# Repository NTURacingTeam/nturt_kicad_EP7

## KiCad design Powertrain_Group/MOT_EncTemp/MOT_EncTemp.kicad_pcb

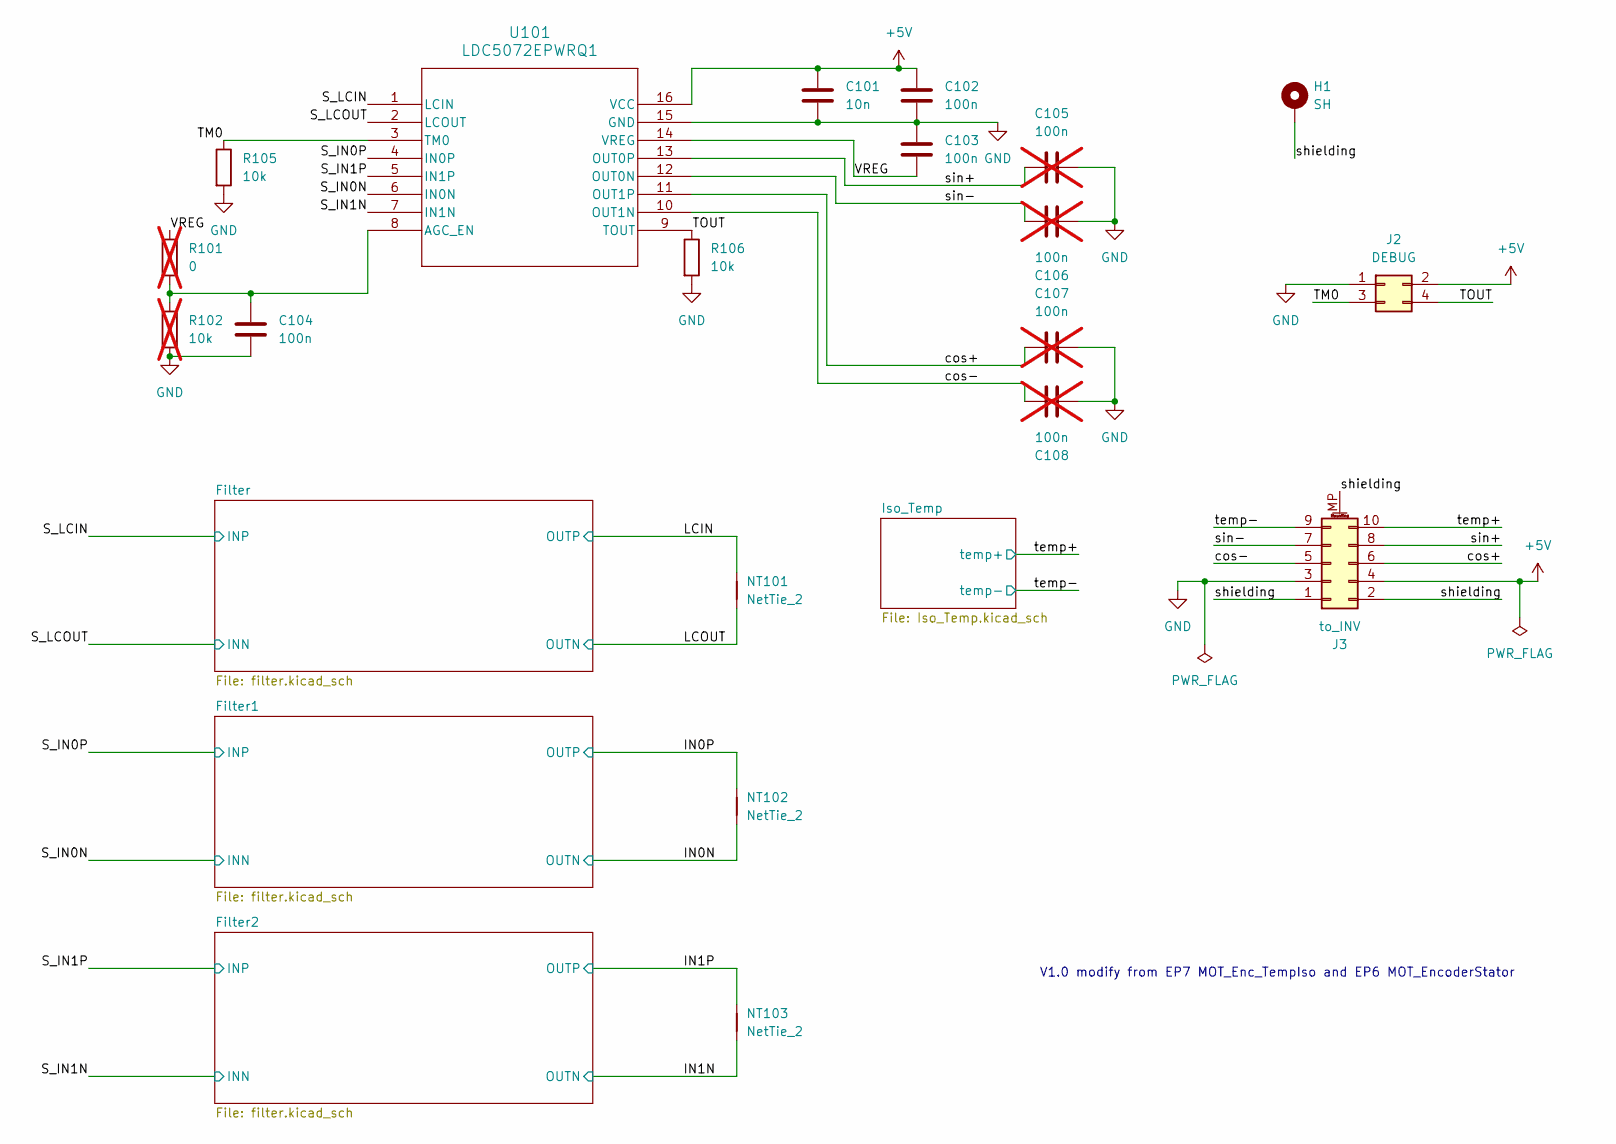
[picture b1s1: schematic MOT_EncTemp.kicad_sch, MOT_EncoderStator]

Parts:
C101: 10n; C_0402_1005Metric
C102, C103: 100n; C_0402_1005Metric
C104: 100n; C_0603_1608Metric
C105, C106, C107, C108: 100n; C_0402_1005Metric; not fitted
H1: SH; MountingHole_3.2mm_M3_Pad_Via
J2: DEBUG; PinHeader_2x02_P2.00mm_Vertical_SMD
J3: to_INV; CONN_2202010000-SD_10P_MOL
NT101, NT102, NT103: NetTie_2; NetTie-2_SMD_Pad0.5mm
R101: 0; R_0603_1608Metric; not fitted
R102: 10k; R_0603_1608Metric; not fitted
R105, R106: 10k; R_0402_1005Metric
U101: LDC5072EPWRQ1; TSSOP-16_4.4x5mm_P0.65mm

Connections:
+5V: C101.1, C102.1, J2.2, J3.4, U101.16 (VCC); also elsewhere on the board
/IN0N: NT102.1; also elsewhere on the board
/IN0P: NT102.2; also elsewhere on the board
/IN1N: NT103.1; also elsewhere on the board
/IN1P: NT103.2; also elsewhere on the board
/LCIN: NT101.2; also elsewhere on the board
/LCOUT: NT101.1; also elsewhere on the board
/S_IN0N: U101.6 (IN0N); also elsewhere on the board
/S_IN0P: U101.4 (IN0P); also elsewhere on the board
/S_IN1N: U101.7 (IN1N); also elsewhere on the board
/S_IN1P: U101.5 (IN1P); also elsewhere on the board
/S_LCIN: U101.1 (LCIN); also elsewhere on the board
/S_LCOUT: U101.2 (LCOUT); also elsewhere on the board
/TM0: J2.3, R105.1, U101.3 (TM0)
/TOUT: J2.4, R106.1, U101.9 (TOUT)
/VREG: C103.2, R101.1, U101.14 (VREG)
/cos+: C107.1, J3.6, U101.11 (OUT1P)
/cos-: C108.2, J3.5, U101.10 (OUT1N)
/shielding: H1.1, J3.1, J3.2, J3.MP (MountPin)
/sin+: C105.1, J3.8, U101.13 (OUT0P)
/sin-: C106.2, J3.7, U101.12 (OUT0N)
/temp+: J3.10; also elsewhere on the board
/temp-: J3.9; also elsewhere on the board
GND: C101.2, C102.2, C103.1, C104.2, C105.2, C106.1, C107.2, C108.1, J2.1, J3.3, R102.2, R105.2, R106.2, U101.15 (GND); also elsewhere on the board
unnamed: C104.1, R101.2, R102.1, U101.8 (AGC_EN)

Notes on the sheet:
V1.0 modify from EP7 MOT_Enc_TempIso and EP6 MOT_EncoderStator

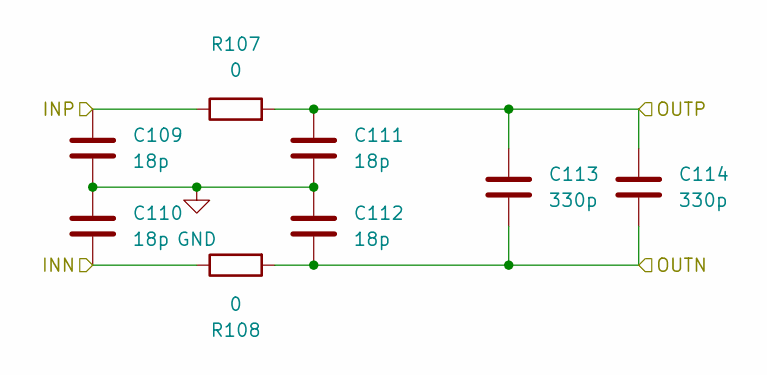
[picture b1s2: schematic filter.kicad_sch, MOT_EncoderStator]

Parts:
C109, C110, C111, C112: 18p; C_0402_1005Metric
C113, C114: 330p; C_0402_1005Metric
R107, R108: 0; R_0402_1005Metric

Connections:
/LCIN: C111.1, C113.1, C114.1, R107.2; also elsewhere on the board
/LCOUT: C112.2, C113.2, C114.2, R108.2; also elsewhere on the board
/S_LCIN: C109.1, R107.1; also elsewhere on the board
/S_LCOUT: C110.2, R108.1; also elsewhere on the board
GND: C109.2, C110.1, C111.2, C112.1; also elsewhere on the board

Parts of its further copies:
C115, C116, C117, C118, C121, C122, C123, C124: 18p; C_0402_1005Metric
C119, C120, C125, C126: 330p; C_0402_1005Metric
R109, R110, R111, R112: 0; R_0402_1005Metric

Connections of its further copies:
/IN0N: C118.2, C119.2, C120.2, R110.2; also elsewhere on the board
/IN0P: C117.1, C119.1, C120.1, R109.2; also elsewhere on the board
/IN1N: C124.2, C125.2, C126.2, R112.2; also elsewhere on the board
/IN1P: C123.1, C125.1, C126.1, R111.2; also elsewhere on the board
/S_IN0N: C116.2, R110.1; also elsewhere on the board
/S_IN0P: C115.1, R109.1; also elsewhere on the board
/S_IN1N: C122.2, R112.1; also elsewhere on the board
/S_IN1P: C121.1, R111.1; also elsewhere on the board
GND: C115.2, C116.1, C117.2, C118.1, C121.2, C122.1, C123.2, C124.1; also elsewhere on the board

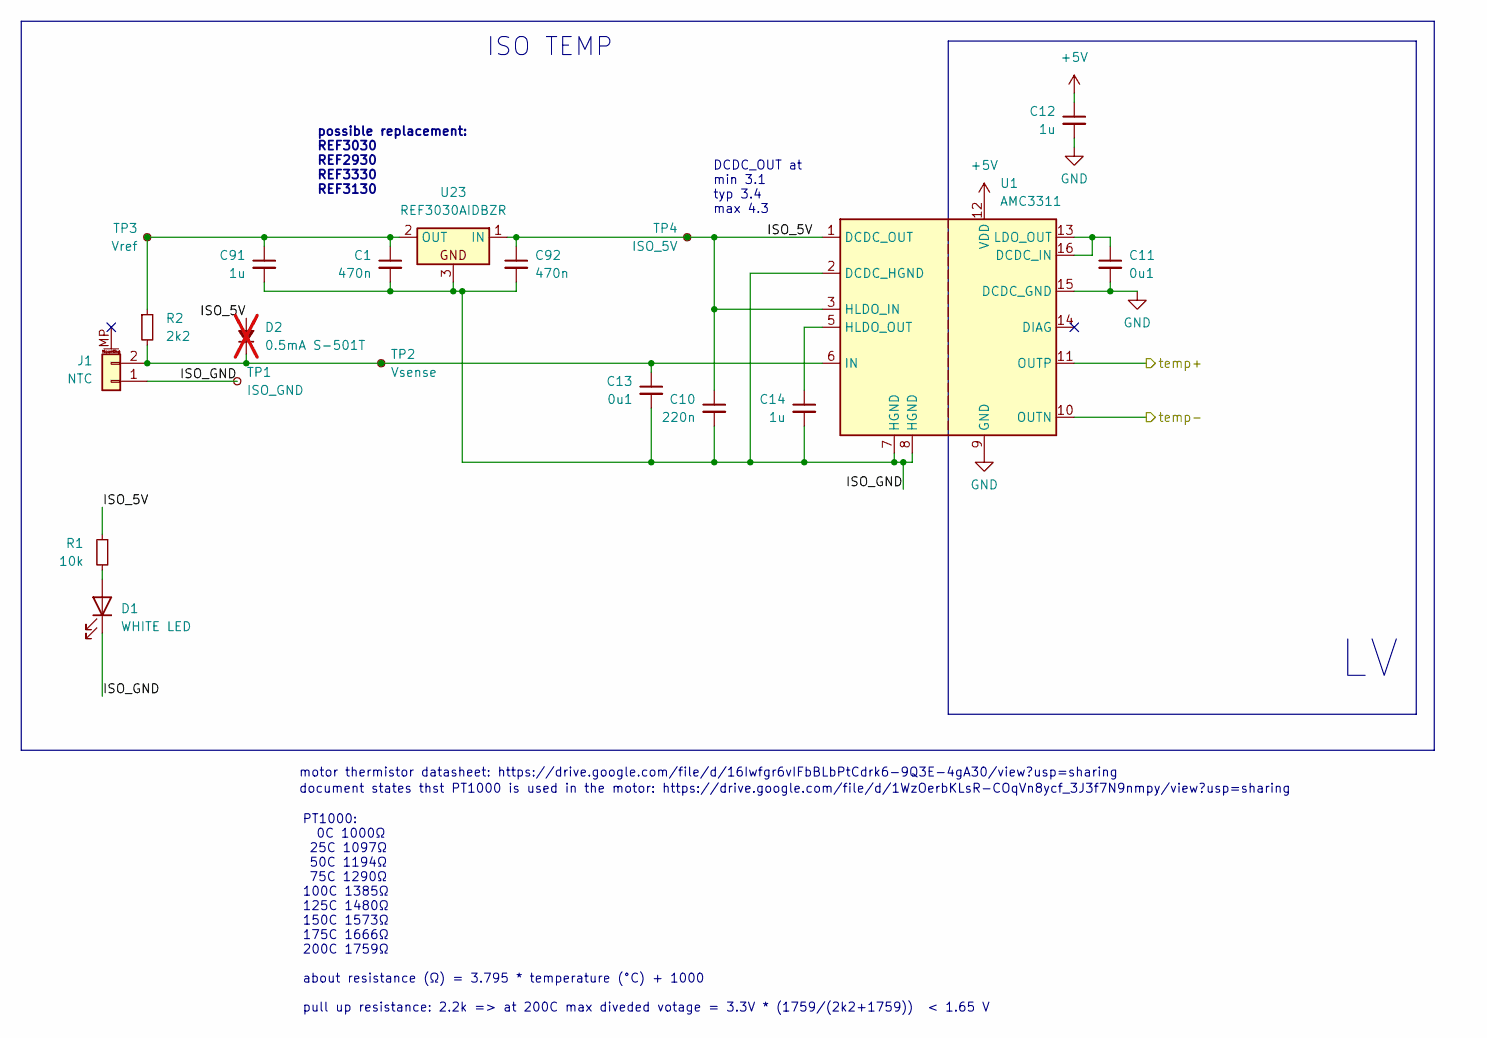
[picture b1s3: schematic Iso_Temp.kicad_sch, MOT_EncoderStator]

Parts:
C1, C92: 470n; C_0603_1608Metric_Pad1.08x0.95mm_HandSolder
C10: 220n; C_0603_1608Metric_Pad1.08x0.95mm_HandSolder
C11, C13: 0u1; C_0603_1608Metric_Pad1.08x0.95mm_HandSolder
C12, C14, C91: 1u; C_0603_1608Metric_Pad1.08x0.95mm_HandSolder
D1: WHITE LED; LED_0603_1608Metric_Pad1.05x0.95mm_HandSolder
D2: 0.5mA S-501T; D_1206_3216Metric_Pad1.42x1.75mm_HandSolder; not fitted
J1: NTC; JST_PH_S2B-PH-SM4-TB_1x02-1MP_P2.00mm_Horizontal
R1: 10k; R_0603_1608Metric_Pad0.98x0.95mm_HandSolder
R2: 2k2; R_0603_1608Metric_Pad0.98x0.95mm_HandSolder
TP1: ISO_GND; TestPoint_Pad_D1.0mm
TP2: Vsense; TestPoint_Pad_D1.0mm
TP3: Vref; TestPoint_Pad_D1.0mm
TP4: ISO_5V; TestPoint_Pad_D1.0mm
U1: AMC3311; SOIC-16W_7.5x10.3mm_P1.27mm
U23: REF3030AIDBZR; SOT-23

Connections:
+5V: C12.1, U1.12 (VDD); also elsewhere on the board
/Iso_Temp/ISO_5V: C10.1, C92.1, D2.2 (A), R1.1, TP4.1, U1.1 (DCDC_OUT), U1.3 (HLDO_IN), U23.1 (IN)
/Iso_Temp/ISO_GND: C1.2, C10.2, C13.2, C14.2, C91.2, C92.2, D1.1 (K), J1.1, TP1.1, U1.2 (DCDC_HGND), U1.7 (HGND), U1.8 (HGND), U23.3
/temp+: U1.11 (OUTP); also elsewhere on the board
/temp-: U1.10 (OUTN); also elsewhere on the board
GND: C11.2, C12.2, U1.9 (GND), U1.15 (DCDC_GND); also elsewhere on the board
unnamed: D1.2 (A), R1.2
unnamed: C13.1, D2.1 (K), J1.2, R2.2, TP2.1, U1.6 (IN)
unnamed: C11.1, U1.13 (LDO_OUT), U1.16 (DCDC_IN)
unnamed: C14.1, U1.5 (HLDO_OUT)
unnamed: C1.1, C91.1, R2.1, TP3.1, U23.2 (OUT)

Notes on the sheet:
possible replacement: REF3030 REF2930 REF3330 REF3130
motor thermistor datasheet: https://drive.google.com/file/d/16Iwfgr6vIFbBLbPtCdrk6-9Q3E-4gA30/view?usp=sharing
PT1000: 0C 1000Ω 25C 1097Ω 50C 1194Ω 75C 1290Ω 100C 1385Ω 125C 1480Ω 150C 1573Ω 175C 1666Ω 200C 1759Ω about resistance (Ω) = 3.795 * temperature (°C) + 1000 pull up resistance: 2.2k => at 200C max diveded votage = 3.3V * (1759/(2k2+1759)) < 1.65 V
ISO TEMP
DCDC_OUT at min 3.1 typ 3.4 max 4.3
document states thst PT1000 is used in the motor: https://drive.google.com/file/d/1WzOerbKLsR-COqVn8ycf_3J3f7N9nmpy/view?usp=sharing

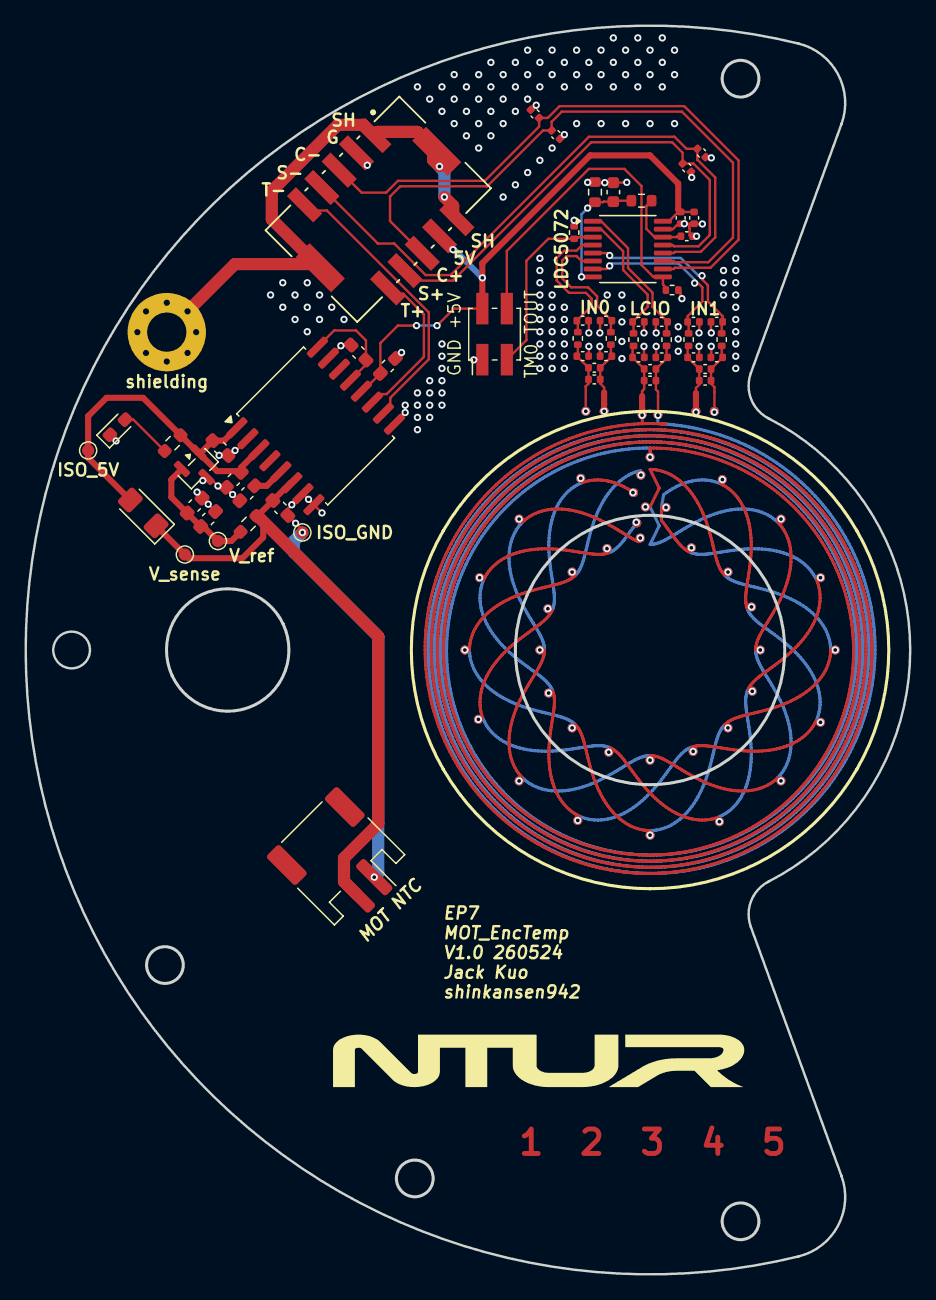
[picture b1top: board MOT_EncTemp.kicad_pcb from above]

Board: 4 copper layers, 72.2 x 102.0 mm, 62 parts (0 on the bottom side), 32 nets.

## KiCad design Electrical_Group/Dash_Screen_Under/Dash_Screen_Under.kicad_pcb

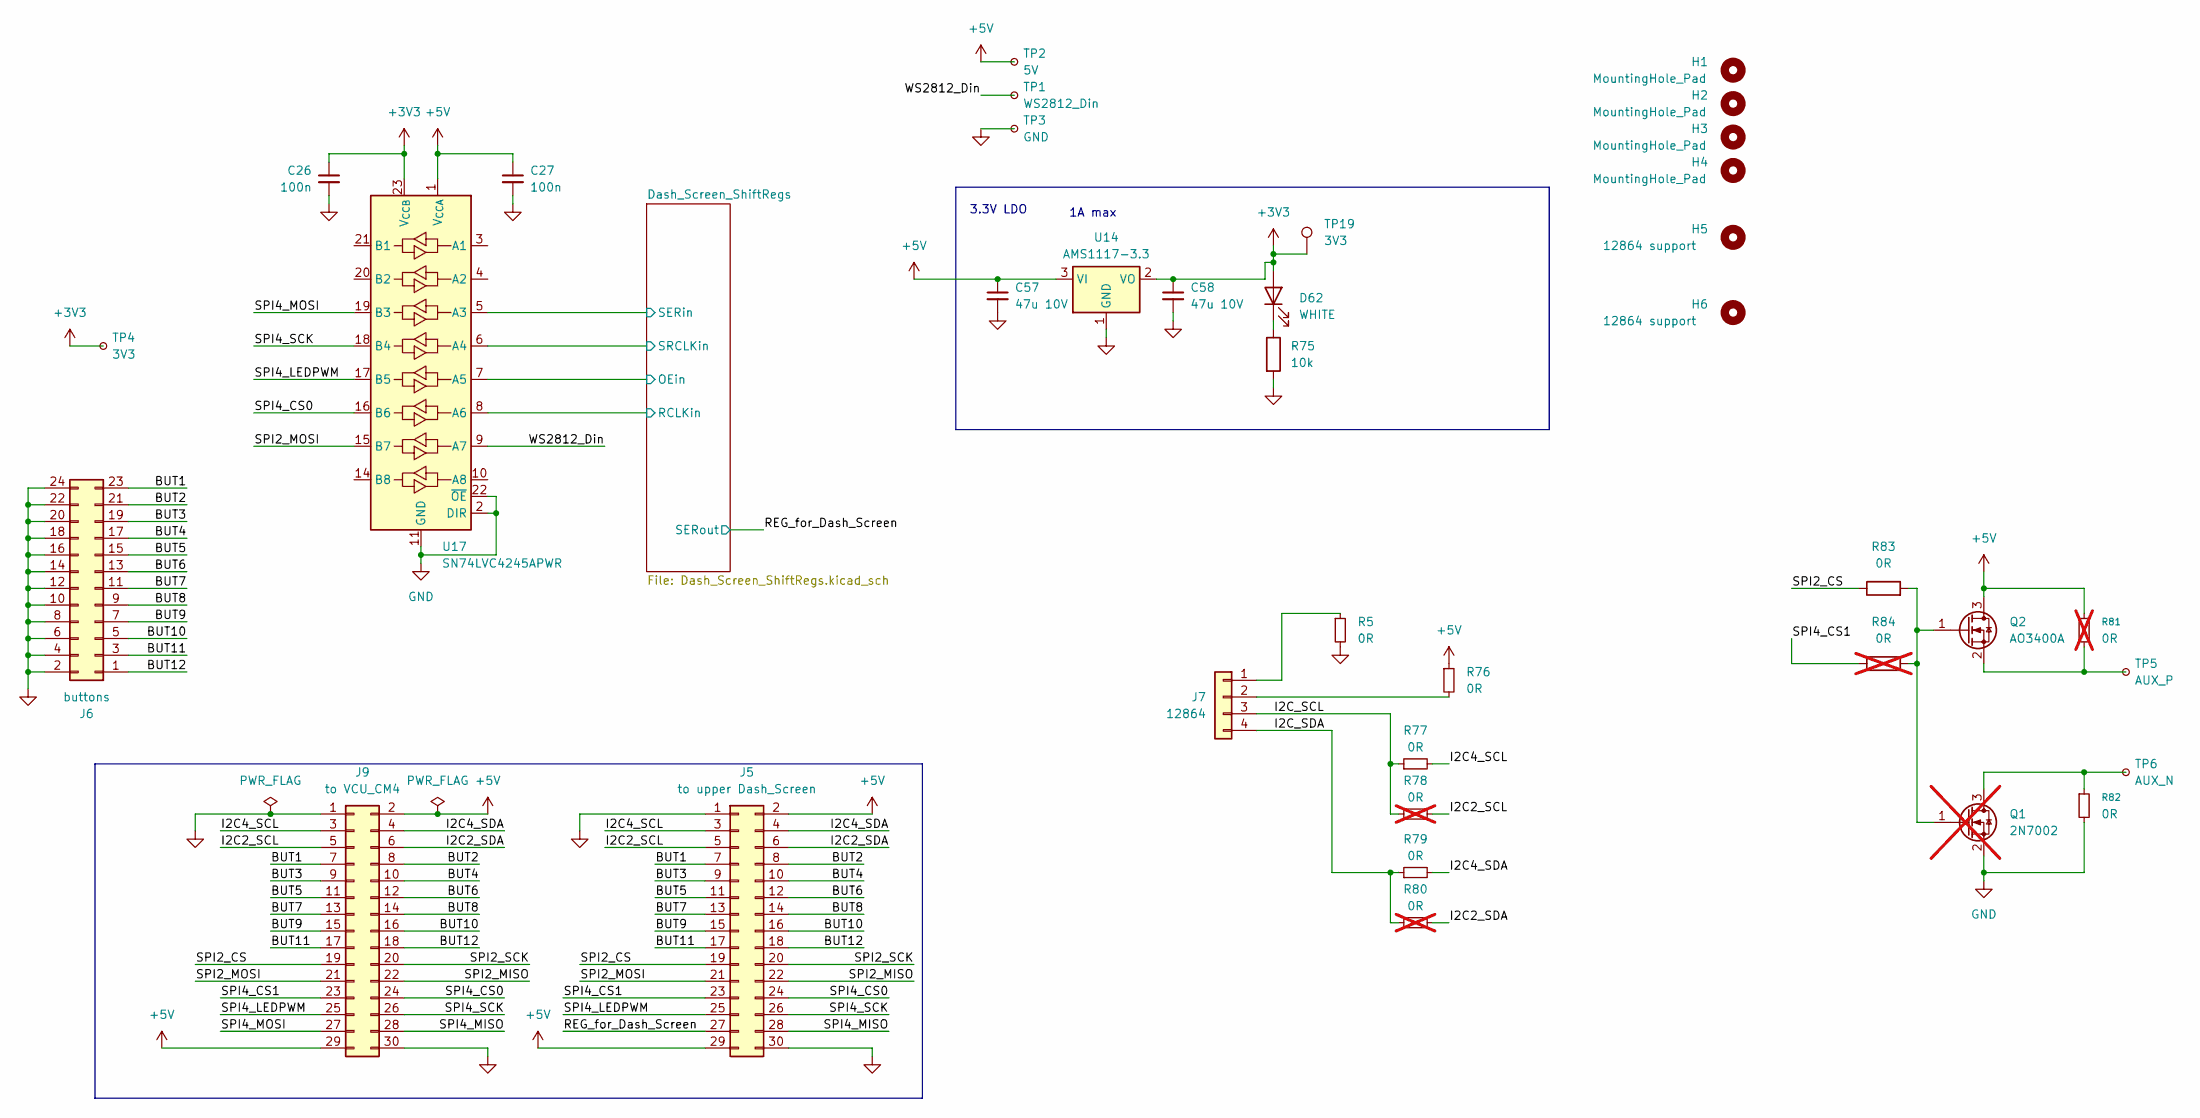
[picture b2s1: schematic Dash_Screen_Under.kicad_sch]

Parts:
C26, C27: 100n; C_0603_1608Metric
C57, C58: 47u 10V; C_1206_3216Metric
D62: WHITE; LED_0603_1608Metric
H1, H2, H3, H4: MountingHole_Pad; MountingHole_3.2mm_M3
H5, H6: 12864 support; MountingHole_3.2mm_M3
J5: to upper Dash_Screen; PinHeader_2x15_P2.00mm_Vertical_SMD
J6: buttons; PinHeader_2x12_P2.00mm_Horizontal
J7: 12864; 12864_1.3_I2C
J9: to VCU_CM4; PinSocket_2x15_P2.00mm_Vertical_SMD
Q1: 2N7002; SOT-23; not fitted
Q2: AO3400A; SOT-23
R5, R76, R77, R79, R82: 0R; R_0805_2012Metric_Pad1.20x1.40mm_HandSolder
R75: 10k; R_0603_1608Metric
R78, R80, R81: 0R; R_0805_2012Metric_Pad1.20x1.40mm_HandSolder; not fitted
R83: 0R; R_0603_1608Metric
R84: 0R; R_0603_1608Metric; not fitted
TP1: WS2812_Din; edge_pad_1.4mm_0.7mm
TP2: 5V; edge_pad_1.4mm_0.7mm
TP3: GND; edge_pad_1.4mm_0.7mm
TP4: 3V3; edge_pad_1.4mm_0.7mm
TP5: AUX_P; edge_pad_1.4mm_0.7mm
TP6: AUX_N; edge_pad_1.4mm_0.7mm
TP19: 3V3; TestPoint_Pad_D1.0mm
U14: AMS1117-3.3; SOT-223-3_TabPin2
U17: SN74LVC4245APWR; TSSOP-24_4.4x7.8mm_P0.65mm

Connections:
+3V3: C26.1, C58.1, D62.2 (A), TP4.1, TP19.1, U14.2 (VO), U17.23 (V_{CCB}), U17.24 (V_{CCB})
+5V: C27.1, C57.1, J5.2, J5.29, J9.2, J9.29, Q2.3 (D), R76.1, R81.1, TP2.1, U14.3 (VI), U17.1 (V_{CCA}); also elsewhere on the board
/BUT1: J5.7, J6.23, J9.7
/BUT2: J5.8, J6.21, J9.8
/BUT3: J5.9, J6.19, J9.9
/BUT4: J5.10, J6.17, J9.10
/BUT5: J5.11, J6.15, J9.11
/BUT6: J5.12, J6.13, J9.12
/BUT7: J5.13, J6.11, J9.13
/BUT8: J5.14, J6.9, J9.14
/BUT9: J5.15, J6.7, J9.15
/BUT10: J5.16, J6.5, J9.16
/BUT11: J5.17, J6.3, J9.17
/BUT12: J5.18, J6.1, J9.18
/Dash_Screen_ShiftRegs/OE: U17.7 (A5); also elsewhere on the board
/Dash_Screen_ShiftRegs/RCLK: U17.8 (A6); also elsewhere on the board
/Dash_Screen_ShiftRegs/SER: U17.5 (A3); also elsewhere on the board
/Dash_Screen_ShiftRegs/SRCLK: U17.6 (A4); also elsewhere on the board
/I2C2_SCL: J5.5, J9.5, R78.2
/I2C2_SDA: J5.6, J9.6, R80.2
/I2C4_SCL: J5.3, J9.3, R77.2
/I2C4_SDA: J5.4, J9.4, R79.2
/I2C_SCL: J7.3, R77.1, R78.1
/I2C_SDA: J7.4, R79.1, R80.1
/REG_for_Dash_Screen: J5.27; also elsewhere on the board
/SPI2_CS: J5.19, J9.19, R83.1
/SPI2_MISO: J5.22, J9.22
/SPI2_MOSI: J5.21, J9.21, U17.15 (B7)
/SPI2_SCK: J5.20, J9.20
/SPI4_CS0: J5.24, J9.24, U17.16 (B6)
/SPI4_CS1: J5.23, J9.23, R84.1
/SPI4_LEDPWM: J5.25, J9.25, U17.17 (B5)
/SPI4_MISO: J5.28, J9.28
/SPI4_MOSI: J9.27, U17.19 (B3)
/SPI4_SCK: J5.26, J9.26, U17.18 (B4)
/WS2812_Din: TP1.1, U17.9 (A7)
GND: C26.2, C27.2, C57.2, C58.2, J5.1, J5.30, J6.2, J6.4, J6.6, J6.8, J6.10, J6.12, J6.14, J6.16, J6.18, J6.20, J6.22, J6.24, J9.1, J9.30, Q1.2 (S), R5.2, R75.2, R82.2, TP3.1, U14.1 (GND), U17.2 (DIR), U17.11 (GND), U17.12 (GND), U17.13 (GND), U17.22 (~OE); also elsewhere on the board
unnamed: D62.1 (K), R75.1
unnamed: J7.1, R5.1
unnamed: J7.2, R76.2
unnamed: Q1.3 (D), R82.1, TP6.1
unnamed: Q1.1 (G), Q2.1 (G), R83.2, R84.2
unnamed: Q2.2 (S), R81.2, TP5.1

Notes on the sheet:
3.3V LDO
1A max

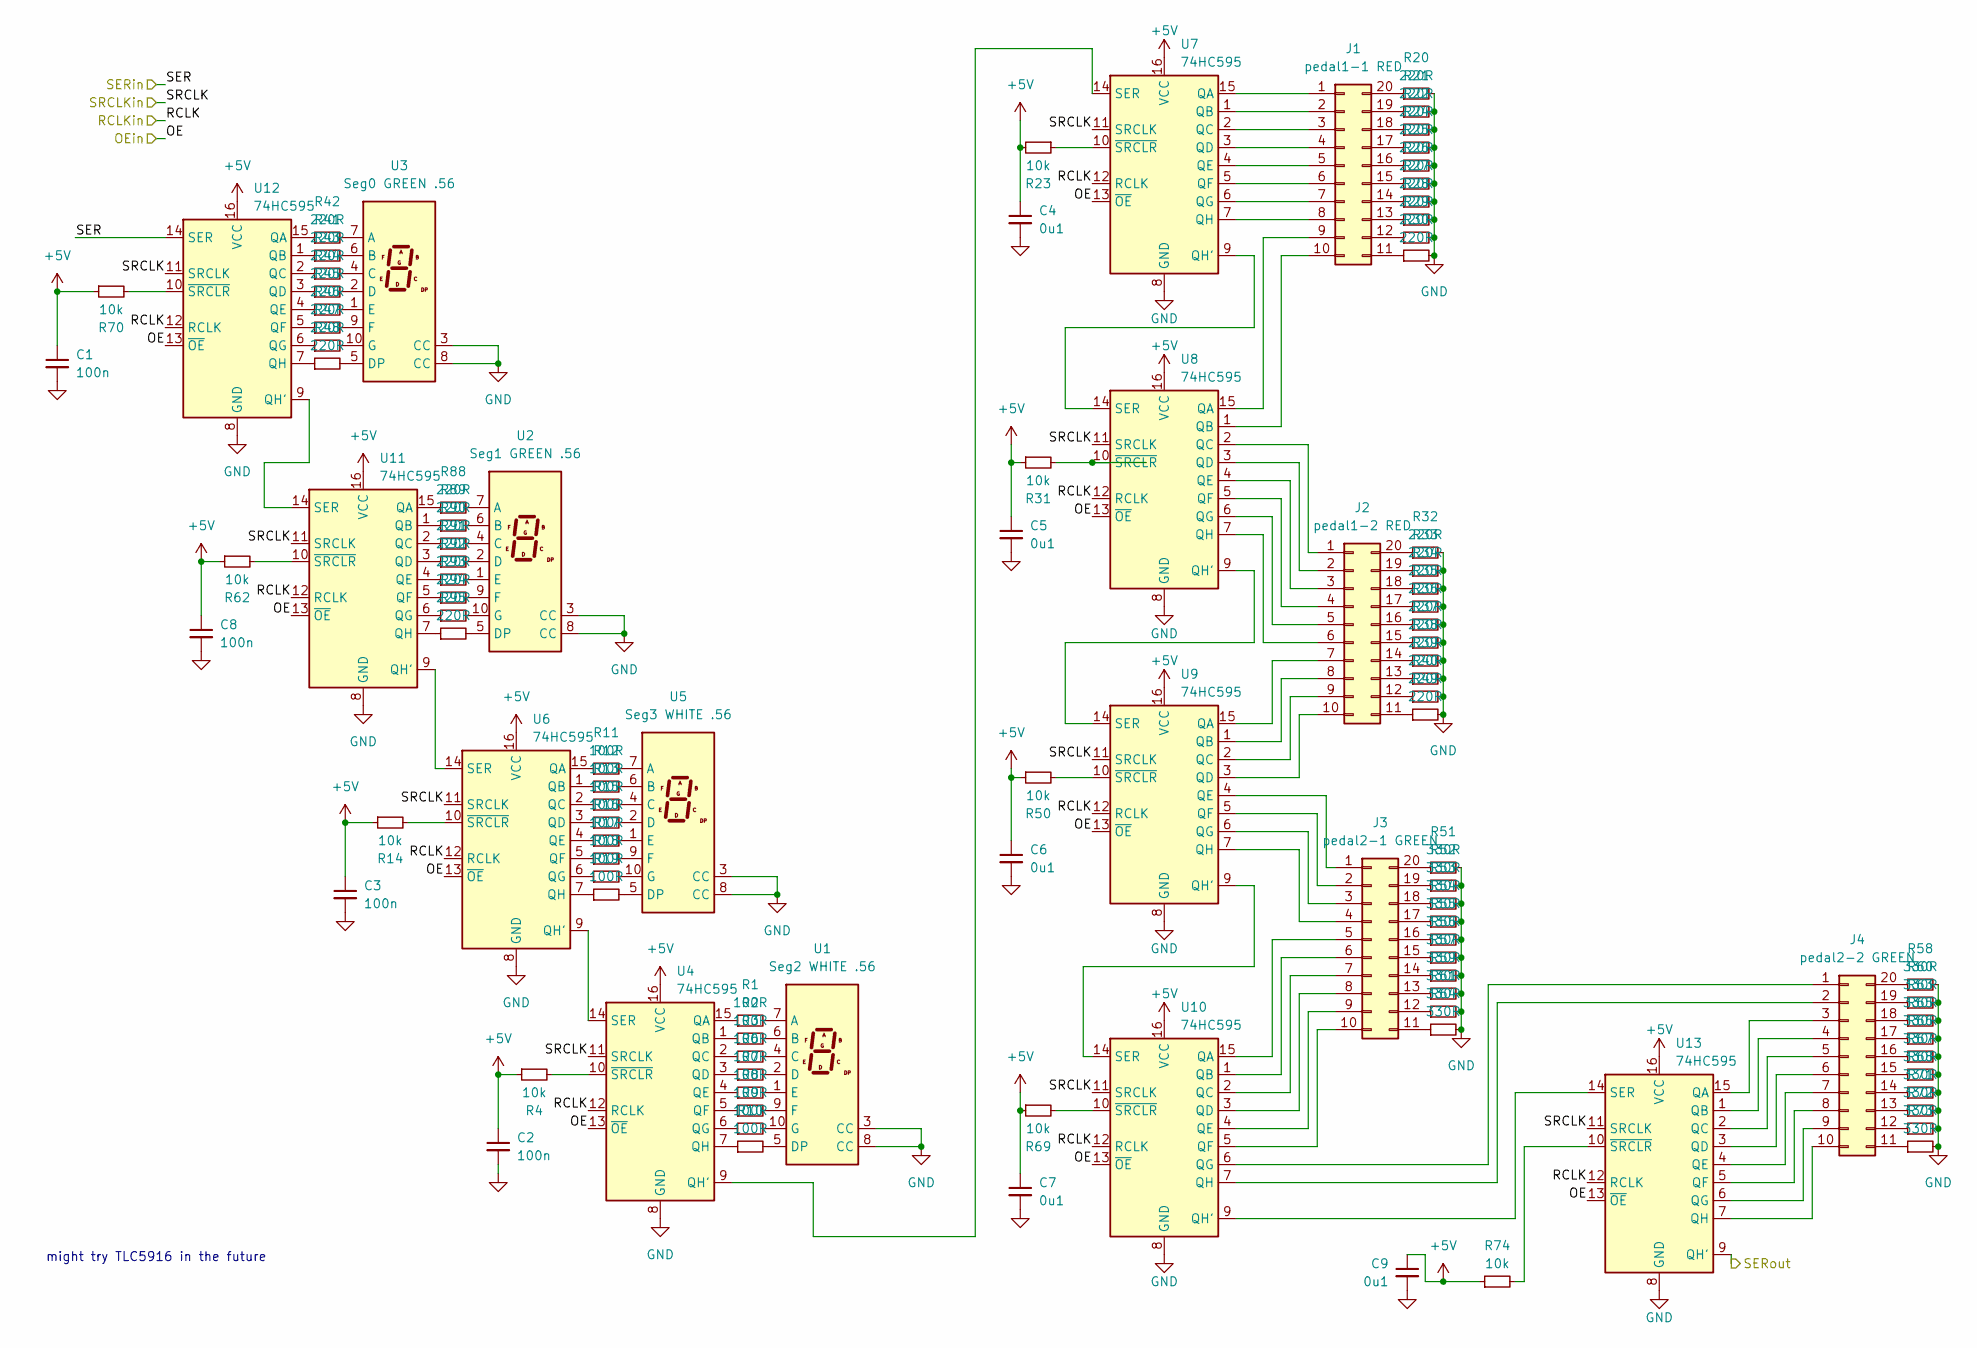
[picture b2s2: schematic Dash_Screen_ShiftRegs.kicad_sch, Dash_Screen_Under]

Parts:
C1, C2, C3, C8: 100n; C_0603_1608Metric
C4, C5, C6, C7, C9: 0u1; C_0805_2012Metric
J1: pedal1-1 RED; DIP-20_W7.62mm
J2: pedal1-2 RED; DIP-20_W7.62mm
J3: pedal2-1 GREEN; DIP-20_W7.62mm
J4: pedal2-2 GREEN; DIP-20_W7.62mm
R1, R2, R3, R6, R7, R8, R9, R10, R11, R12, R13, R15, R16, R17, R18, R19: 100R; R_0603_1608Metric_Pad0.98x0.95mm_HandSolder
R4, R14, R23, R31, R50, R62, R69, R70, R74: 10k; R_0603_1608Metric
R20, R21, R22, R24, R25, R26, R27, R28, R29, R30, R32, R33, R34, R35, R36, R37, R38, R39, R40, R41, R42, R43, R44, R45, R46, R47, R48, R49, R88, R89, R90, R91, R92, R93, R94, R95: 220R; R_0603_1608Metric_Pad0.98x0.95mm_HandSolder
R51, R52, R53, R54, R55, R56, R57, R58, R59, R60, R61, R63, R64, R65, R66, R67, R68, R71, R72, R73: 330R; R_0603_1608Metric_Pad0.98x0.95mm_HandSolder
U1: Seg2 WHITE .56; 7SegmentLED_LTS6760_LTS6780
U2: Seg1 GREEN .56; 7SegmentLED_LTS6760_LTS6780
U3: Seg0 GREEN .56; 7SegmentLED_LTS6760_LTS6780
U4, U6, U7, U8, U9, U10, U11, U12, U13: 74HC595; SOIC-16_3.9x9.9mm_P1.27mm
U5: Seg3 WHITE .56; 7SegmentLED_LTS6760_LTS6780

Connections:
+5V: C1.1, C2.1, C3.1, C4.1, C5.1, C6.1, C7.1, C8.1, C9.1, R4.1, R14.1, R23.2, R31.1, R50.1, R62.1, R69.1, R70.1, R74.1, U4.16 (VCC), U6.16 (VCC), U7.16 (VCC), U8.16 (VCC), U9.16 (VCC), U10.16 (VCC), U11.16 (VCC), U12.16 (VCC), U13.16 (VCC); also elsewhere on the board
/Dash_Screen_ShiftRegs/OE: U4.13 (~OE), U6.13 (~OE), U7.13 (~OE), U8.13 (~OE), U9.13 (~OE), U10.13 (~OE), U11.13 (~OE), U12.13 (~OE), U13.13 (~OE); also elsewhere on the board
/Dash_Screen_ShiftRegs/RCLK: U4.12 (RCLK), U6.12 (RCLK), U7.12 (RCLK), U8.12 (RCLK), U9.12 (RCLK), U10.12 (RCLK), U11.12 (RCLK), U12.12 (RCLK), U13.12 (RCLK); also elsewhere on the board
/Dash_Screen_ShiftRegs/SER: U12.14 (SER); also elsewhere on the board
/Dash_Screen_ShiftRegs/SRCLK: U4.11 (SRCLK), U6.11 (SRCLK), U7.11 (SRCLK), U8.11 (SRCLK), U9.11 (SRCLK), U10.11 (SRCLK), U11.11 (SRCLK), U12.11 (SRCLK), U13.11 (SRCLK); also elsewhere on the board
/REG_for_Dash_Screen: U13.9 (QH'); also elsewhere on the board
GND: C1.2, C2.2, C3.2, C4.2, C5.2, C6.2, C7.2, C8.2, C9.2, R20.2, R21.2, R22.2, R24.2, R25.2, R26.2, R27.2, R28.2, R29.2, R30.2, R32.2, R33.2, R34.2, R35.2, R36.2, R37.2, R38.2, R39.2, R40.2, R49.2, R51.2, R52.2, R53.2, R54.2, R55.2, R56.2, R57.2, R58.2, R59.2, R60.2, R61.2, R63.2, R64.2, R65.2, R66.2, R67.2, R68.2, R71.2, R72.2, R73.2, U1.3 (CC), U1.8 (CC), U2.3 (CC), U2.8 (CC), U3.3 (CC), U3.8 (CC), U4.8 (GND), U5.3 (CC), U5.8 (CC), U6.8 (GND), U7.8 (GND), U8.8 (GND), U9.8 (GND), U10.8 (GND), U11.8 (GND), U12.8 (GND), U13.8 (GND); also elsewhere on the board
unnamed: J1.1, U7.15 (QA)
unnamed: J1.2, U7.1 (QB)
unnamed: J1.3, U7.2 (QC)
unnamed: J1.4, U7.3 (QD)
unnamed: J1.5, U7.4 (QE)
unnamed: J1.6, U7.5 (QF)
unnamed: J1.7, U7.6 (QG)
unnamed: J1.8, U7.7 (QH)
unnamed: J1.9, U8.15 (QA)
unnamed: J1.10, U8.1 (QB)
unnamed: J1.11, R30.1
unnamed: J1.12, R29.1
unnamed: J1.13, R28.1
unnamed: J1.14, R27.1
unnamed: J1.15, R26.1
unnamed: J1.16, R25.1
unnamed: J1.17, R24.1
unnamed: J1.18, R22.1
unnamed: J1.19, R21.1
unnamed: J1.20, R20.1
unnamed: J2.1, U8.2 (QC)
unnamed: J2.2, U8.3 (QD)
unnamed: J2.3, U8.4 (QE)
unnamed: J2.4, U8.5 (QF)
unnamed: J2.5, U8.6 (QG)
unnamed: J2.6, U8.7 (QH)
unnamed: J2.7, U9.15 (QA)
unnamed: J2.8, U9.1 (QB)
unnamed: J2.9, U9.2 (QC)
unnamed: J2.10, U9.3 (QD)
unnamed: J2.11, R49.1
unnamed: J2.12, R40.1
unnamed: J2.13, R39.1
unnamed: J2.14, R38.1
unnamed: J2.15, R37.1
unnamed: J2.16, R36.1
unnamed: J2.17, R35.1
unnamed: J2.18, R34.1
unnamed: J2.19, R33.1
unnamed: J2.20, R32.1
unnamed: J3.1, U9.4 (QE)
unnamed: J3.2, U9.5 (QF)
unnamed: J3.3, U9.6 (QG)
unnamed: J3.4, U9.7 (QH)
unnamed: J3.5, U10.15 (QA)
unnamed: J3.6, U10.1 (QB)
unnamed: J3.7, U10.2 (QC)
unnamed: J3.8, U10.3 (QD)
unnamed: J3.9, U10.4 (QE)
unnamed: J3.10, U10.5 (QF)
unnamed: J3.11, R64.1
unnamed: J3.12, R61.1
unnamed: J3.13, R59.1
unnamed: J3.14, R57.1
unnamed: J3.15, R56.1
unnamed: J3.16, R55.1
unnamed: J3.17, R54.1
unnamed: J3.18, R53.1
unnamed: J3.19, R52.1
unnamed: J3.20, R51.1
unnamed: J4.1, U10.6 (QG)
unnamed: J4.2, U10.7 (QH)
unnamed: J4.3, U13.15 (QA)
unnamed: J4.4, U13.1 (QB)
unnamed: J4.5, U13.2 (QC)
unnamed: J4.6, U13.3 (QD)
unnamed: J4.7, U13.4 (QE)
unnamed: J4.8, U13.5 (QF)
unnamed: J4.9, U13.6 (QG)
unnamed: J4.10, U13.7 (QH)
unnamed: J4.11, R73.1
unnamed: J4.12, R72.1
unnamed: J4.13, R71.1
unnamed: J4.14, R68.1
unnamed: J4.15, R67.1
unnamed: J4.16, R66.1
unnamed: J4.17, R65.1
unnamed: J4.18, R63.1
unnamed: J4.19, R60.1
unnamed: J4.20, R58.1
unnamed: R1.2, U1.7 (A)
unnamed: R2.2, U1.6 (B)
unnamed: R3.2, U1.4 (C)
unnamed: R6.2, U1.2 (D)
unnamed: R10.2, U1.5 (DP)
unnamed: R7.2, U1.1 (E)
unnamed: R8.2, U1.9 (F)
unnamed: R9.2, U1.10 (G)
unnamed: R88.2, U2.7 (A)
unnamed: R89.2, U2.6 (B)
unnamed: R90.2, U2.4 (C)
unnamed: R91.2, U2.2 (D)
unnamed: R95.2, U2.5 (DP)
unnamed: R92.2, U2.1 (E)
unnamed: R93.2, U2.9 (F)
unnamed: R94.2, U2.10 (G)
unnamed: R42.2, U3.7 (A)
unnamed: R41.2, U3.6 (B)
unnamed: R43.2, U3.4 (C)
unnamed: R44.2, U3.2 (D)
unnamed: R48.2, U3.5 (DP)
unnamed: R45.2, U3.1 (E)
unnamed: R46.2, U3.9 (F)
unnamed: R47.2, U3.10 (G)
unnamed: R1.1, U4.15 (QA)
unnamed: R2.1, U4.1 (QB)
unnamed: R3.1, U4.2 (QC)
unnamed: R6.1, U4.3 (QD)
unnamed: R7.1, U4.4 (QE)
unnamed: R8.1, U4.5 (QF)
unnamed: R9.1, U4.6 (QG)
unnamed: U4.9 (QH'), U7.14 (SER)
unnamed: R10.1, U4.7 (QH)
unnamed: U4.14 (SER), U6.9 (QH')
unnamed: R4.2, U4.10 (~SRCLR)
unnamed: R11.2, U5.7 (A)
unnamed: R12.2, U5.6 (B)
unnamed: R13.2, U5.4 (C)
unnamed: R15.2, U5.2 (D)
unnamed: R19.2, U5.5 (DP)
unnamed: R16.2, U5.1 (E)
unnamed: R17.2, U5.9 (F)
unnamed: R18.2, U5.10 (G)
unnamed: R11.1, U6.15 (QA)
unnamed: R12.1, U6.1 (QB)
unnamed: R13.1, U6.2 (QC)
unnamed: R15.1, U6.3 (QD)
unnamed: R16.1, U6.4 (QE)
unnamed: R17.1, U6.5 (QF)
unnamed: R18.1, U6.6 (QG)
unnamed: R19.1, U6.7 (QH)
unnamed: R14.2, U6.10 (~SRCLR)
unnamed: U7.9 (QH'), U8.14 (SER)
unnamed: R23.1, U7.10 (~SRCLR)
unnamed: U8.9 (QH'), U9.14 (SER)
unnamed: R31.2, U8.10 (~SRCLR)
unnamed: R50.2, U9.10 (~SRCLR)
unnamed: U10.9 (QH'), U13.14 (SER)
unnamed: U9.9 (QH'), U10.14 (SER)
unnamed: R69.2, U10.10 (~SRCLR)
unnamed: R88.1, U11.15 (QA)
unnamed: R89.1, U11.1 (QB)
unnamed: R90.1, U11.2 (QC)
unnamed: R91.1, U11.3 (QD)
unnamed: R92.1, U11.4 (QE)
unnamed: R93.1, U11.5 (QF)
unnamed: R94.1, U11.6 (QG)
unnamed: U6.14 (SER), U11.9 (QH')
unnamed: R95.1, U11.7 (QH)
unnamed: U11.14 (SER), U12.9 (QH')
unnamed: R62.2, U11.10 (~SRCLR)
unnamed: R42.1, U12.15 (QA)
unnamed: R41.1, U12.1 (QB)
unnamed: R43.1, U12.2 (QC)
unnamed: R44.1, U12.3 (QD)
unnamed: R45.1, U12.4 (QE)
unnamed: R46.1, U12.5 (QF)
unnamed: R47.1, U12.6 (QG)
unnamed: R48.1, U12.7 (QH)
unnamed: R70.2, U12.10 (~SRCLR)
unnamed: R74.2, U13.10 (~SRCLR)

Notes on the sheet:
might try TLC5916 in the future

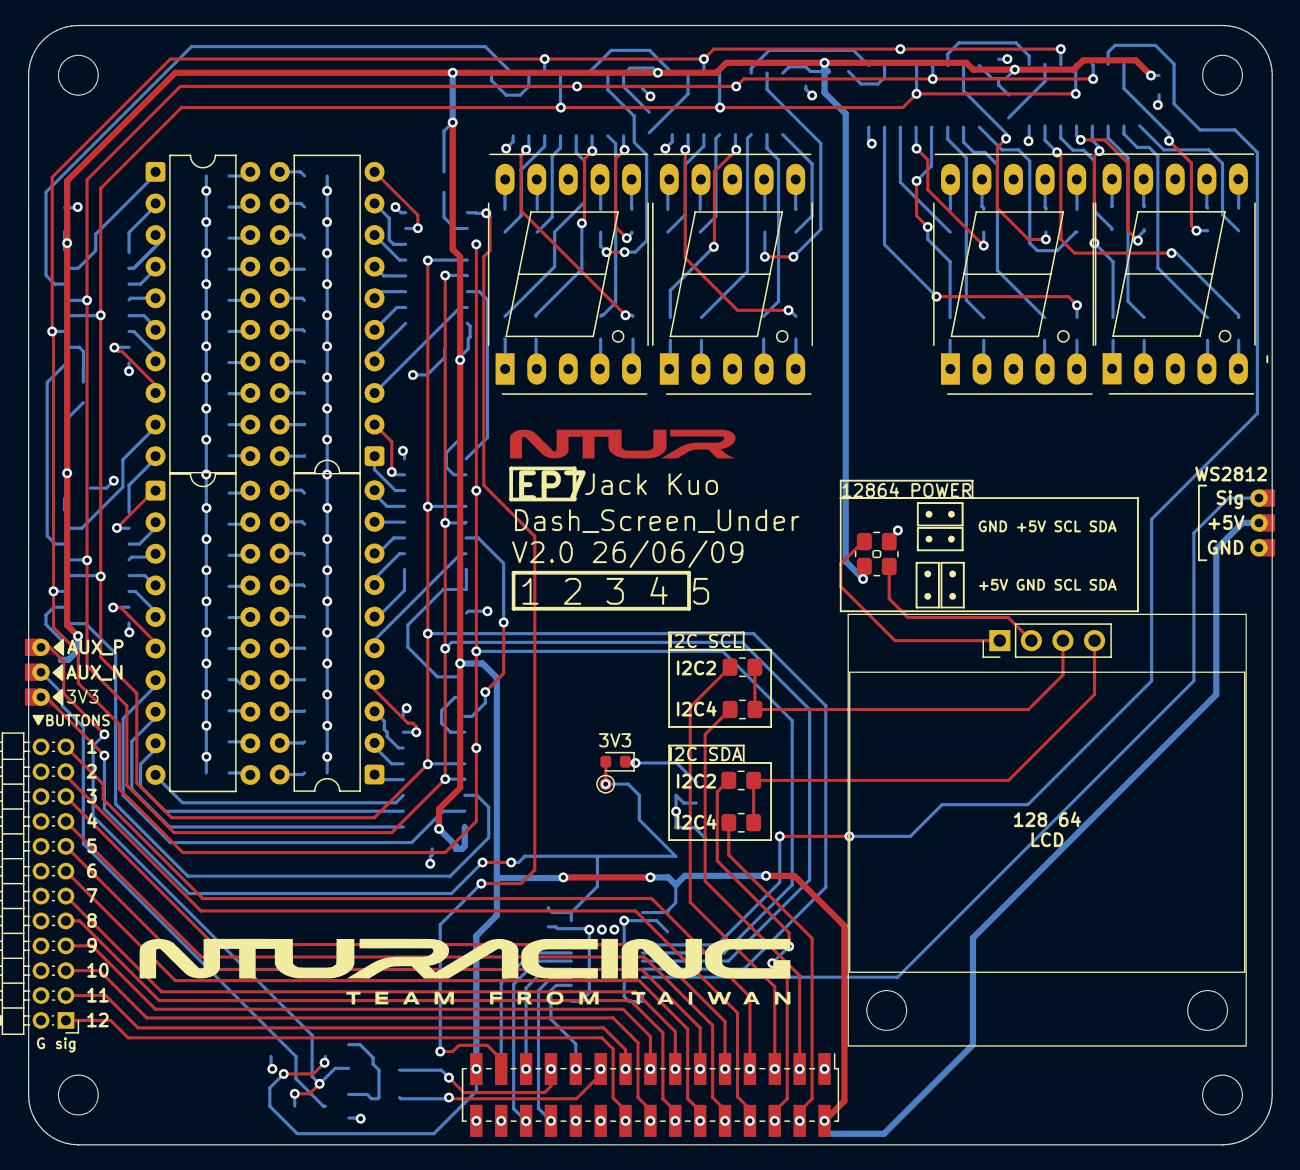
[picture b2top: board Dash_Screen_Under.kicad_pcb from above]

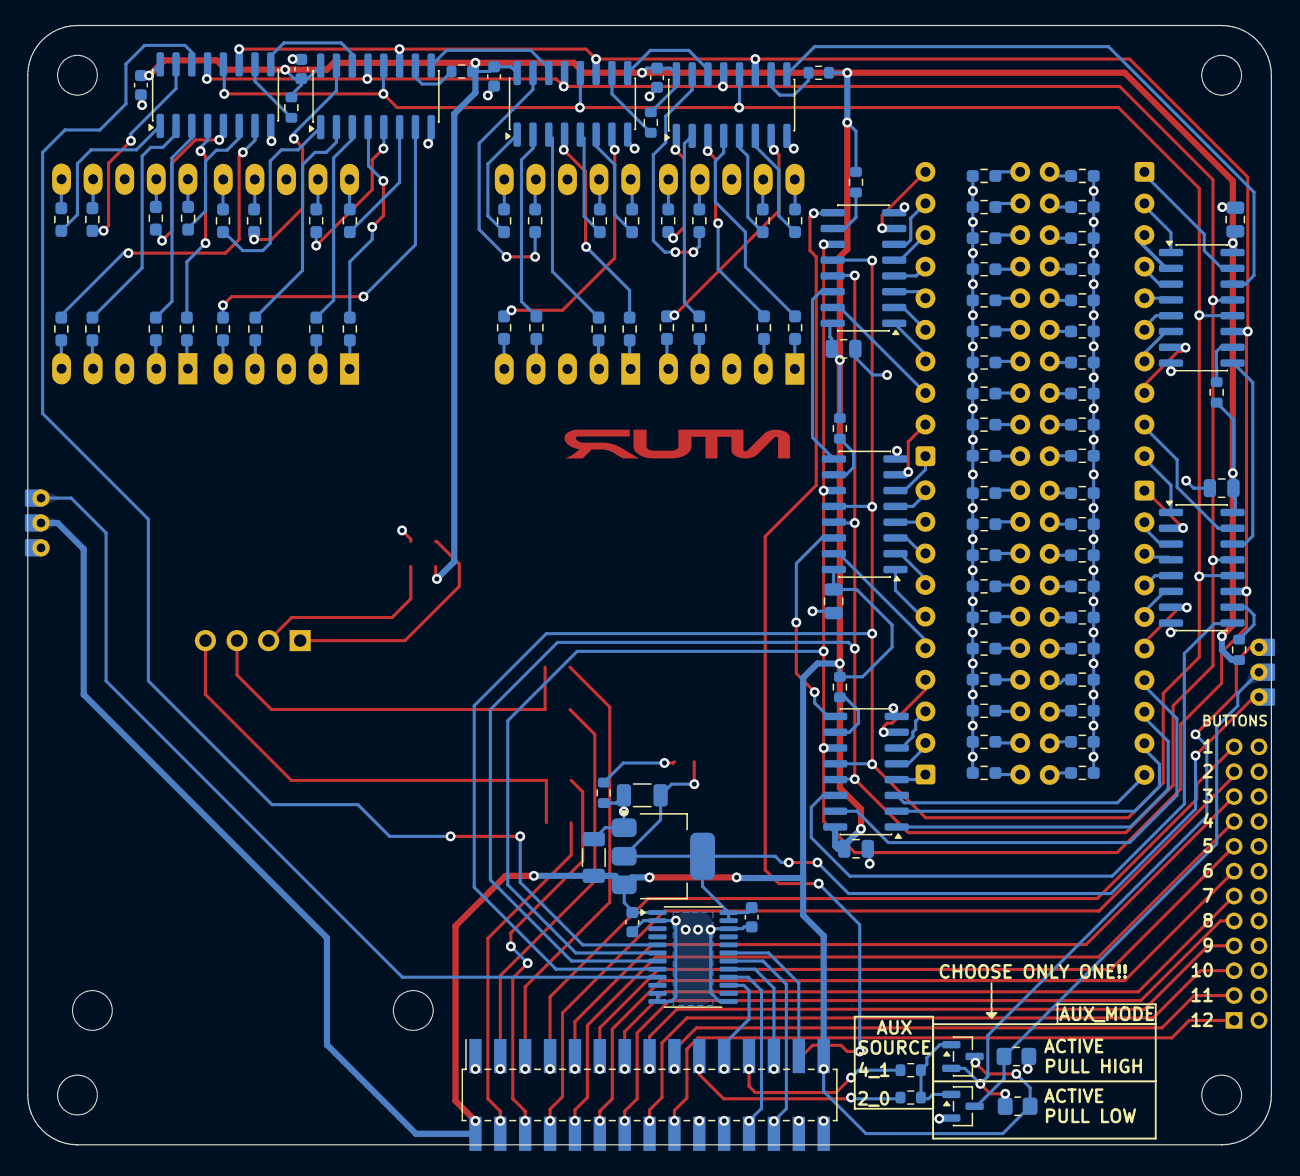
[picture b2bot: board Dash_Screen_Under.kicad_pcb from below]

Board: 4 copper layers, 100.0 x 90.0 mm, 144 parts (113 on the bottom side), 204 nets.
